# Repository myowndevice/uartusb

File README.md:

Данный репозитарий содержит информацию по прибору USB \ Serial
Если вы будете скачивать файлы через web не забудьте скачать общую папку Kicadlib

Если вы решили заняться электроникой, то вам просто необходим USB-Serial конвертер.
Вы его можете сделать самостоятельно по данной [инструкции](http://myowndevice.ru/index.php/pribory/item/7-usb-uart-konverter).

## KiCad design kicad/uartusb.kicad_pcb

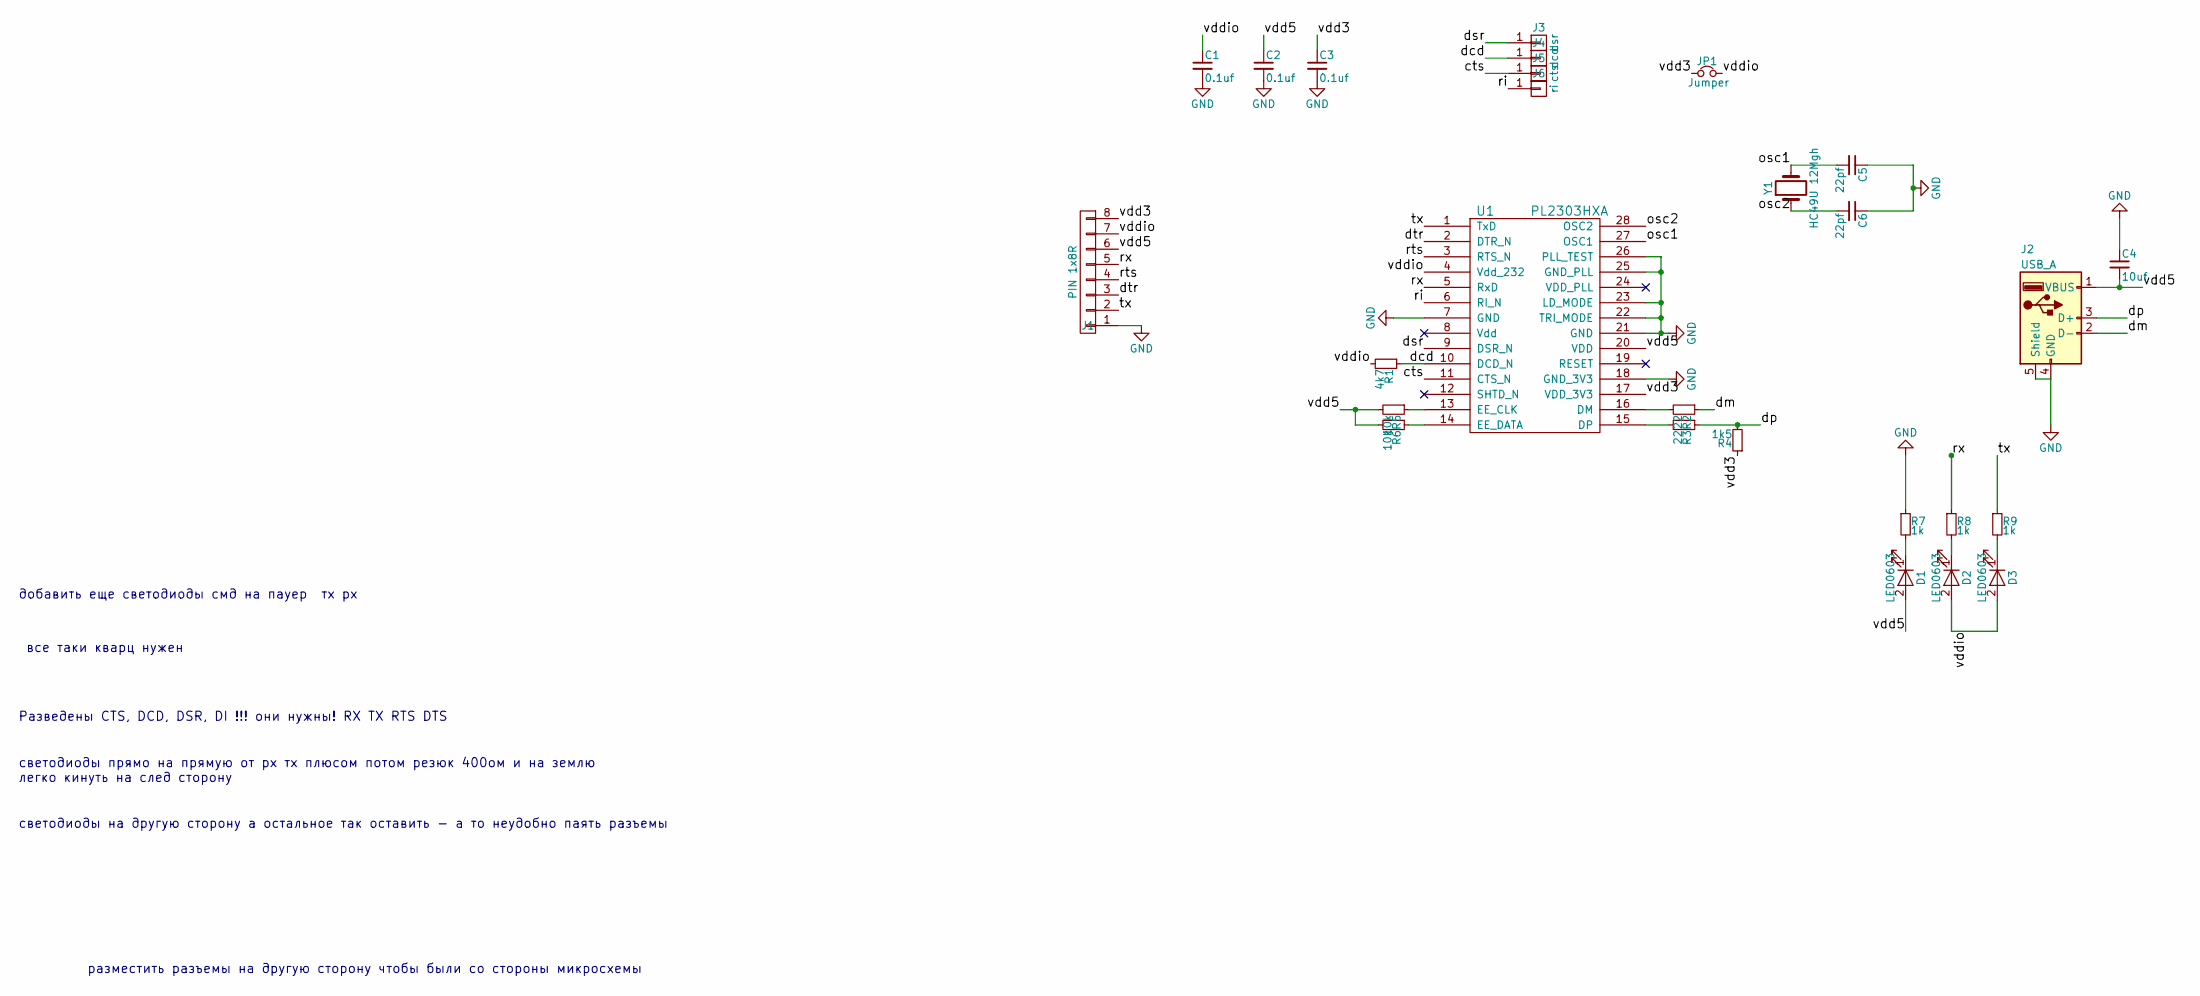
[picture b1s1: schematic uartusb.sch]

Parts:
C1, C2, C3: 0.1uf; C_0603_HandSoldering
C4: 10uf; R_0805_HandSoldering
C5, C6: 22pf; C_0603_HandSoldering
D1, D2, D3: LED0603; LED_0603_HandSoldering
J1: PIN 1x8R; Pin_Header_Angled_1x08_Pitch2.54mm
J2: USB_A; USB_A_male
J3: dsr; wirepadme
J4: dcd; wirepadme
J5: cts; wirepadme
J6: ri; wirepadme
JP1: Jumper; Pin_Header_Straight_1x02_Pitch2.54mm
R1: 4k7; R_0603_HandSoldering
R2, R3: 22; R_0603_HandSoldering
R4: 1k5; R_0603_HandSoldering
R5, R6: 10k; R_0603_HandSoldering
R7, R8, R9: 1k; R_0603_HandSoldering
U1: PL2303HXA; SSOP-28_5.3x10.2mm_Pitch0.65mm
Y1: HC49U 12Mgh; Crystal_HC49-4H_Vertical

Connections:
/cts: J5.1, U1.11 (CTS_N)
/dcd: J4.1, R1.1, U1.10 (DCD_N)
/dm: J2.2 (D-), R2.1
/dp: J2.3 (D+), R3.1, R4.2
/dsr: J3.1, U1.9 (DSR_N)
/dtr: J1.3, U1.2 (DTR_N)
/osc1: C5.2, U1.27 (OSC1), Y1.2
/osc2: C6.2, U1.28 (OSC2), Y1.1
/ri: J6.1, U1.6 (RI_N)
/rts: J1.4, U1.3 (RTS_N)
/rx: J1.5, R8.1, U1.5 (RxD)
/tx: J1.2, R9.1, U1.1 (TxD)
/vdd3: C3.1, J1.8, JP1.1, R4.1, U1.17 (VDD_3V3)
/vdd5: C2.1, C4.2, D1.2 (A), J1.6, J2.1 (VBUS), R5.2, R6.2, U1.20 (VDD)
/vddio: C1.1, D2.2 (A), D3.2 (A), J1.7, JP1.2, R1.2, U1.4 (Vdd_232)
GND: C1.2, C2.2, C3.2, C4.1, C5.1, C6.1, J1.1, J2.4 (GND), J2.5 (Shield), R7.1, U1.7 (GND), U1.18 (GND_3V3), U1.21 (GND), U1.22 (TRI_MODE), U1.23 (LD_MODE), U1.25 (GND_PLL), U1.26 (PLL_TEST)
unnamed: D1.1 (K), R7.2
unnamed: D2.1 (K), R8.2
unnamed: D3.1 (K), R9.2
unnamed: R2.2, U1.16 (DM)
unnamed: R3.2, U1.15 (DP)
unnamed: R5.1, U1.13 (EE_CLK)
unnamed: R6.1, U1.14 (EE_DATA)

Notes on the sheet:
добавить еще светодиоды смд на пауер тх рх
разместить разъемы на другую сторону чтобы были со стороны микросхемы
светодиоды на другую сторону а остальное так оставить - а то неудобно паять разъемы
светодиоды прямо на прямую от рх тх плюсом потом резюк 400ом и на землю легко кинуть на след сторону
все таки кварц нужен
Разведены CTS, DCD, DSR, DI !!! они нужны! RX TX RTS DTS

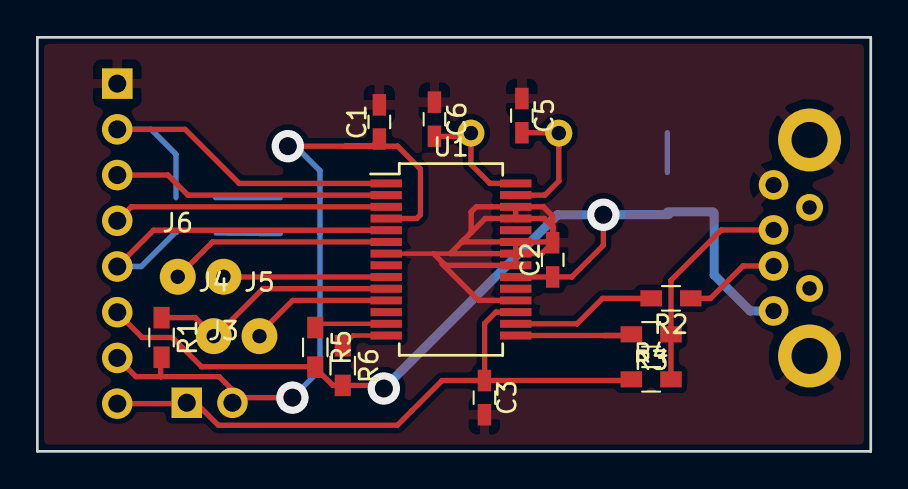
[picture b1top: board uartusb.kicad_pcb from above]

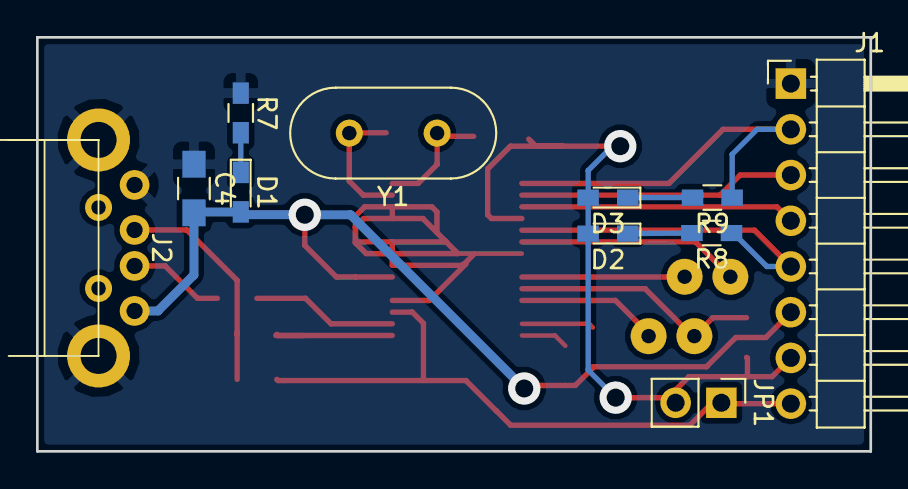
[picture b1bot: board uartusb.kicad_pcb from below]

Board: 2 copper layers, 46.3 x 23.0 mm, 27 parts (11 on the bottom side), 23 nets.

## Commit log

2017-09-09 start
